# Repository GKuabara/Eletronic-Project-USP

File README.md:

# Projeto Fonte Retificadora

## Projeto da Disciplina SSC0180 - Eletrônica para Computação

## Alunos:
Gabriel Alves Kuabara ([KU](https://github.com/GKuabara)) - N° USP 11275043

Guilherme Machado Rios ([Bio](https://github.com/Guibi0)) - N° USP 11222839

Guilherme Lourenço de Toledo ([Vinho](https://github.com/guitld)) - N° USP 11795811

Victor Henrique de Sa Silva ([Spider](https://github.com/VictorHenrique)) - N° USP 11795759

## Instruções:
Projeto de fonte retificadora de tensão contínua entre 3V a 12V com capacidade de 100mA.
A partir de uma tomada de 127V de corrente alternada e frequência de 60Hz, a fonte deve ser capaz de deixar a corrente contínua com tensão ajustável entre 3V a 12V.

## Imagem do Circuito Falstad:

## [Link do Circuito Falstad](https://tinyurl.com/yze7ml4c)

## Imagem do esquemático da PCB no software EAGLE
*O transformador foi separado da placa principal devido ao seu tamanho

## Imagem da PCB no software EAGLE
*O transformador foi separado da placa principal devido ao seu tamanho

## Simulações 3D no softaware Fusion 360
*O transformador foi separado da placa principal devido ao seu tamanho
### Topo

### Frente

### Costas 1

### Costas 2

## Vídeos Explicativos do Circuito:

  [Escolha de cada componente](https://www.youtube.com/watch?v=MA9W5LkvAV4&feature=youtu.be)
  
  [Cálculos relacionados ao circuito](https://www.youtube.com/watch?v=VsMtwc1UD2E)

## Componentes do Circuito:
* **Transformador** - Sendo o primeiro componente da fonte, esse serve para reduzir a tensão de entrada da tomada para o valor de 15V, tensão próxima de funcionamento da fonte. Porém, a corrente continua alternada com semiciclo negativo e positivo, e a tensão oscilando bastante ainda.

* **Diodos** - Responsáveis pela retificação do circuito, isso é, transformar a corrente alternada em corrente contínua atráves da inversão de um dos semiciclos. Na imagem acima, os diodos pares estão polarizados durante o semiciclo positivo e os diodos ímpares estão cortados. Já durante o semiciclo negativo, os diodos assumem papel oposto. Além disso, apesar de termos a corrente contínua, ainda existem variações na tensão quando há a troca de semiciclos denominadas "ripples"(variação residual periodica derivada de uma corrente alternada).

* **Capacitor** - Faz o papel da filtragem de modo a reduzir o "ripple" para maior estabilidade da corrente. Assim, o capacitor carrega durante o pico de tensão, e quando a tensão diminui para o semiciclo inverso, a tensão interna do capacitor supera a tensão do circuito, fazendo com que o capacitor alimente o circuito, logo diminuindo o "ripple".

* **Resistores** - Fazem o papel de proteção dos componentes do circuitos, evitando que a corrente ultrapasse os valores de funcionamento dos componentes evitando que explodam na nossa cara, amém.

* **Potenciometro** - Resistor de resistência variável que permite a variação da tensão entre 3V e 12V. 

* **Diodo Zener** - Regula a tensão máxima do circuito. O zener conduz corrente somente quando acima da corrente de ruptura e assim diminui a corrente para a tensão nominal do diodo. Dessa forma, mantem a tensão entre os seus terminais quando acima da mínima, nesse caso 12V. 

* **Transistor NPN** - Capaz de controlar a corrente elétrica de maneira ajustável.

## Componentes, especificações e valores:
| **Quantidade** | **Componentes**   | **Especificações** | **Valor**|
|----------------|-------------------|--------------------|----------|
|         1x     | [Transformador](https://produto.mercadolivre.com.br/MLB-1299159736-transformador-1515v-1a-trafo-bivolt-_JM?matt_tool=82322591&matt_word&gclid=Cj0KCQjw3Nv3BRC8ARIsAPh8hgKeMy0nJofiC6KaxPgJOotdfYedegX4Cvw1K8ZATrrtRfrb-_nViN8aAoY1EALw_wcB&quantity=1) | 15V | R$ 29.90|
|         4x     | [Diodo](https://www.arduoeletro.com/diodo-1n-4007?utm_source=Site&utm_medium=GoogleMerchant&utm_campaign=GoogleMerchant&gclid=Cj0KCQjw3Nv3BRC8ARIsAPh8hgJ0wxy2Hp_5nHJ2fnSKeIm5tyTmb2PZhb8mVqMMBYZ7-NIENwZE6ToaAscCEALw_wcB) | Normal |  R$ 0.40|
|         1x     | [Capacitor Eletrolítico](https://www.eletrogate.com/capacitor-eletrolitico-1000uf-x-16v?utm_source=Site&utm_medium=GoogleMerchant&utm_campaign=GoogleMerchant&gclid=Cj0KCQjwoub3BRC6ARIsABGhnyZ_RIU0_78Q12_vGcE23LCamEqiIbno5rkSUVdKnD0BTOSjUcxPa7oaAkqBEALw_wcB) | 750uF |  R$ 0.45|
|         1x     | [Resistor](https://produto.mercadolivre.com.br/MLB-1342907792-resistor-330-ohms-100-unidades-_JM?matt_tool=79246729&matt_word&gclid=Cj0KCQjw3Nv3BRC8ARIsAPh8hgLQmDXTySOG5SPVeSkZzxwxIkQ18u9yLq5I2XRCE6nhx1F0_QvOYmUaAspBEALw_wcB&quantity=1) | 330ohms |  R$ 0.13|
|         1x     | [Resistor](https://produto.mercadolivre.com.br/MLB-937733782-kit-10-x-resistor-22k-ohm-14w-1-projeto-arduino-raspberry-_JM?matt_tool=79246729&matt_word&gclid=Cj0KCQjw3Nv3BRC8ARIsAPh8hgKAe7Wy7yk2gXiOZ5dqMArm00GkyamfaNH7T7loakiJhOX3ozAropwaAhECEALw_wcB&quantity=1) | 2.2k |  R$ 0.86|
|         1x     | [Diodo](https://www.americanas.com.br/produto/1397103736?opn=YSMESP&sellerid=4145166000157&epar=bp_pl_00_go_am_todas_geral_gmv&WT.srch=1&acc=e789ea56094489dffd798f86ff51c7a9&i=5dd8ae5049f937f6254fab94&o=5df60079f8e95eac3dac6177&gclid=Cj0KCQjw3Nv3BRC8ARIsAPh8hgIA358SW4MTZbxC3F3oDX6124FH0DvY33t5ULAEiQPJIl66QkP-IVgaApfTEALw_wcB) | Zener 13V |  R$ 0.60|
|         1x     | [Potenciômetro](https://www.baudaeletronica.com.br/potenciometro-linear-de-5k-5000.html) | 5k |  R$ 1.15|
|         1x     | [Transistor](https://www.google.com/aclk?sa=l&ai=DChcSEwjDyLSEq6PqAhUHCJEKHRbGAwYYABAEGgJjZQ&sig=AOD64_1MjzoeLBrcoe0HWlJstQacJ3uwSg&ctype=5&q=&ved=0ahUKEwi_9K-Eq6PqAhX3ErkGHQihCi0Q2CkI0gI&adurl=) | NPN |  R$ 1.75|
| **Total** ||| R$ 38.18 |

## Agradecimentos:
Obrigado Simões pela extrema coerência mostrada em suas atitudes como docente no contexto atual ♡♡

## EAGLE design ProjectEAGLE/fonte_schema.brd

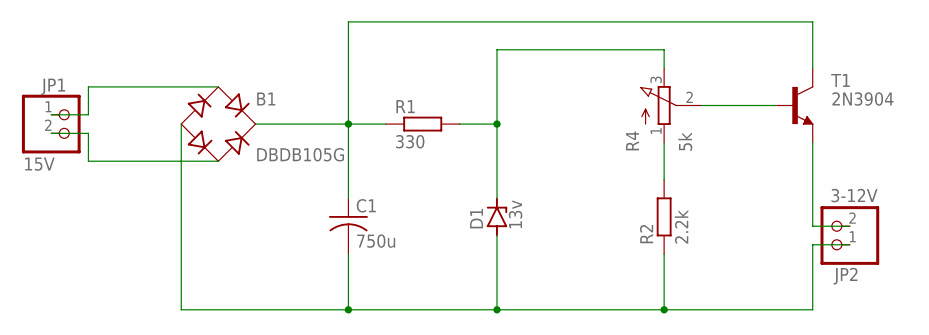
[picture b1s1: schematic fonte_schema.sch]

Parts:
B1: DBDB105G; DB
C1: 750u; C025-025X050
D1: 13v; SOD81
JP1: 15V; 1X02
JP2: 3-12V; 1X02
R1: 330; 0204/7
R2: 2.2k; 0204/7
R4: 5k; 3RP/1610N
T1: 2N3904; TO92

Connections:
unnamed: JP2.2, T1.3 (E)
unnamed: B1.AC1, JP1.1
unnamed: B1.+, C1.1, R1.1, T1.1 (C)
unnamed: D1.C, R1.2, R4.3 (E)
unnamed: B1.AC2, JP1.2
unnamed: R4.2 (S), T1.2 (B)
unnamed: R2.2, R4.1 (A)
unnamed: B1.-, C1.2, D1.A, JP2.1, R2.1

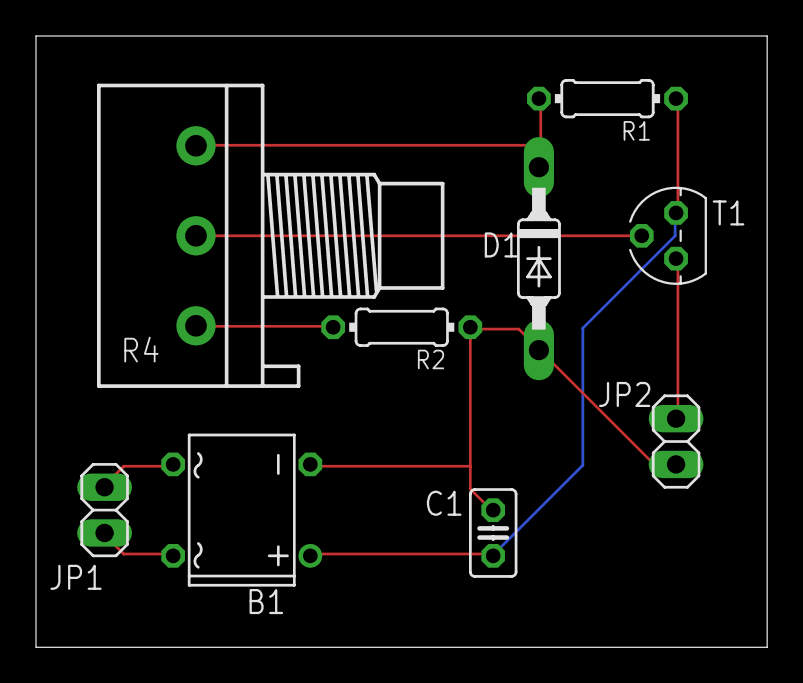
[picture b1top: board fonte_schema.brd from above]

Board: 2 copper layers, 40.6 x 34.0 mm, 9 parts (0 on the bottom side), 8 nets.

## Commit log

2020-06-27 atualizacao do readme
2020-06-27 corrigindo formato do readme
2020-06-27 atualização dnv
2020-06-27 mesma coisa
2020-06-30 add images
2020-06-30 Finalizando
2020-07-08 Final readmeq
2020-07-08 Final readme
2020-07-08 readme final
